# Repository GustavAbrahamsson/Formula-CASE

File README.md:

# Formula-CASE | Miniature Formula-style RC cars!

## ESP32-S3, FreeRTOS, 4WD

## F1-inspired custom steering wheel, with magnetic paddle shifters

## Remote control with "driver POV" video feed

## PCB

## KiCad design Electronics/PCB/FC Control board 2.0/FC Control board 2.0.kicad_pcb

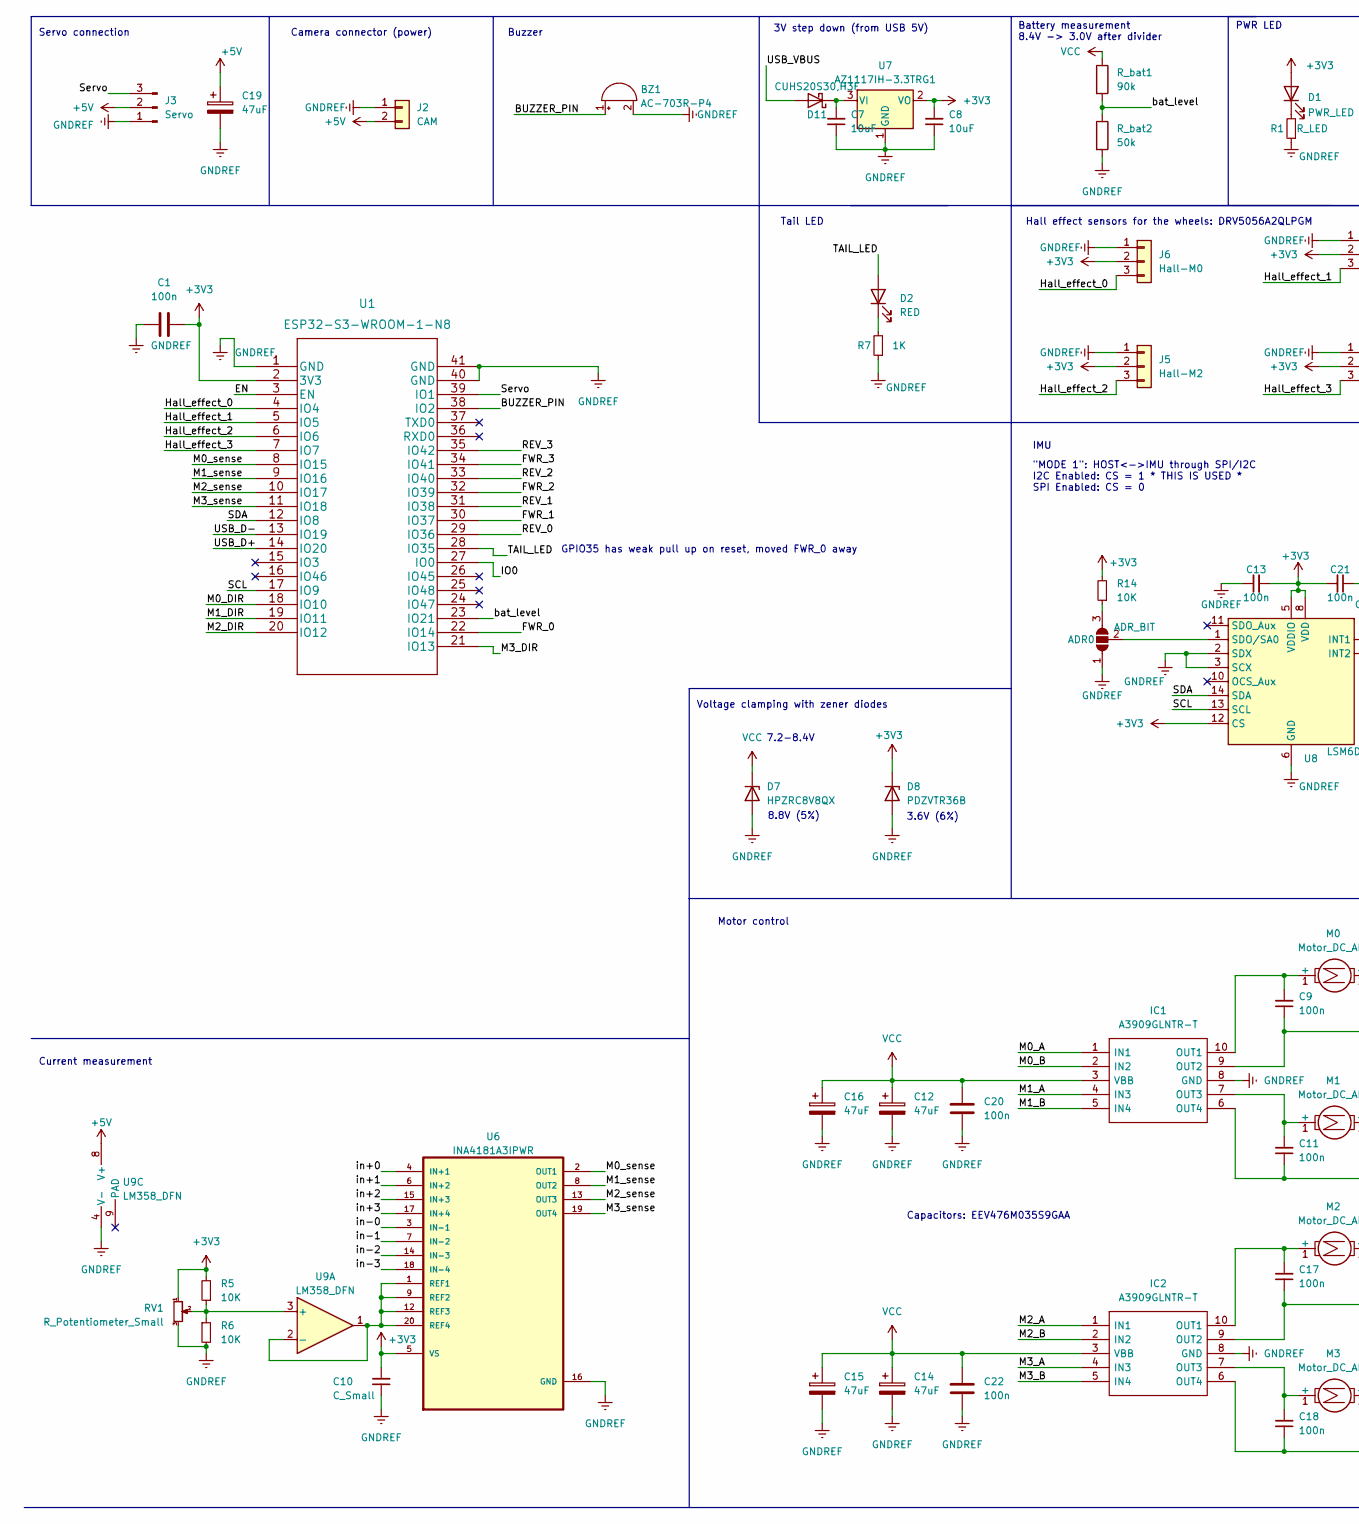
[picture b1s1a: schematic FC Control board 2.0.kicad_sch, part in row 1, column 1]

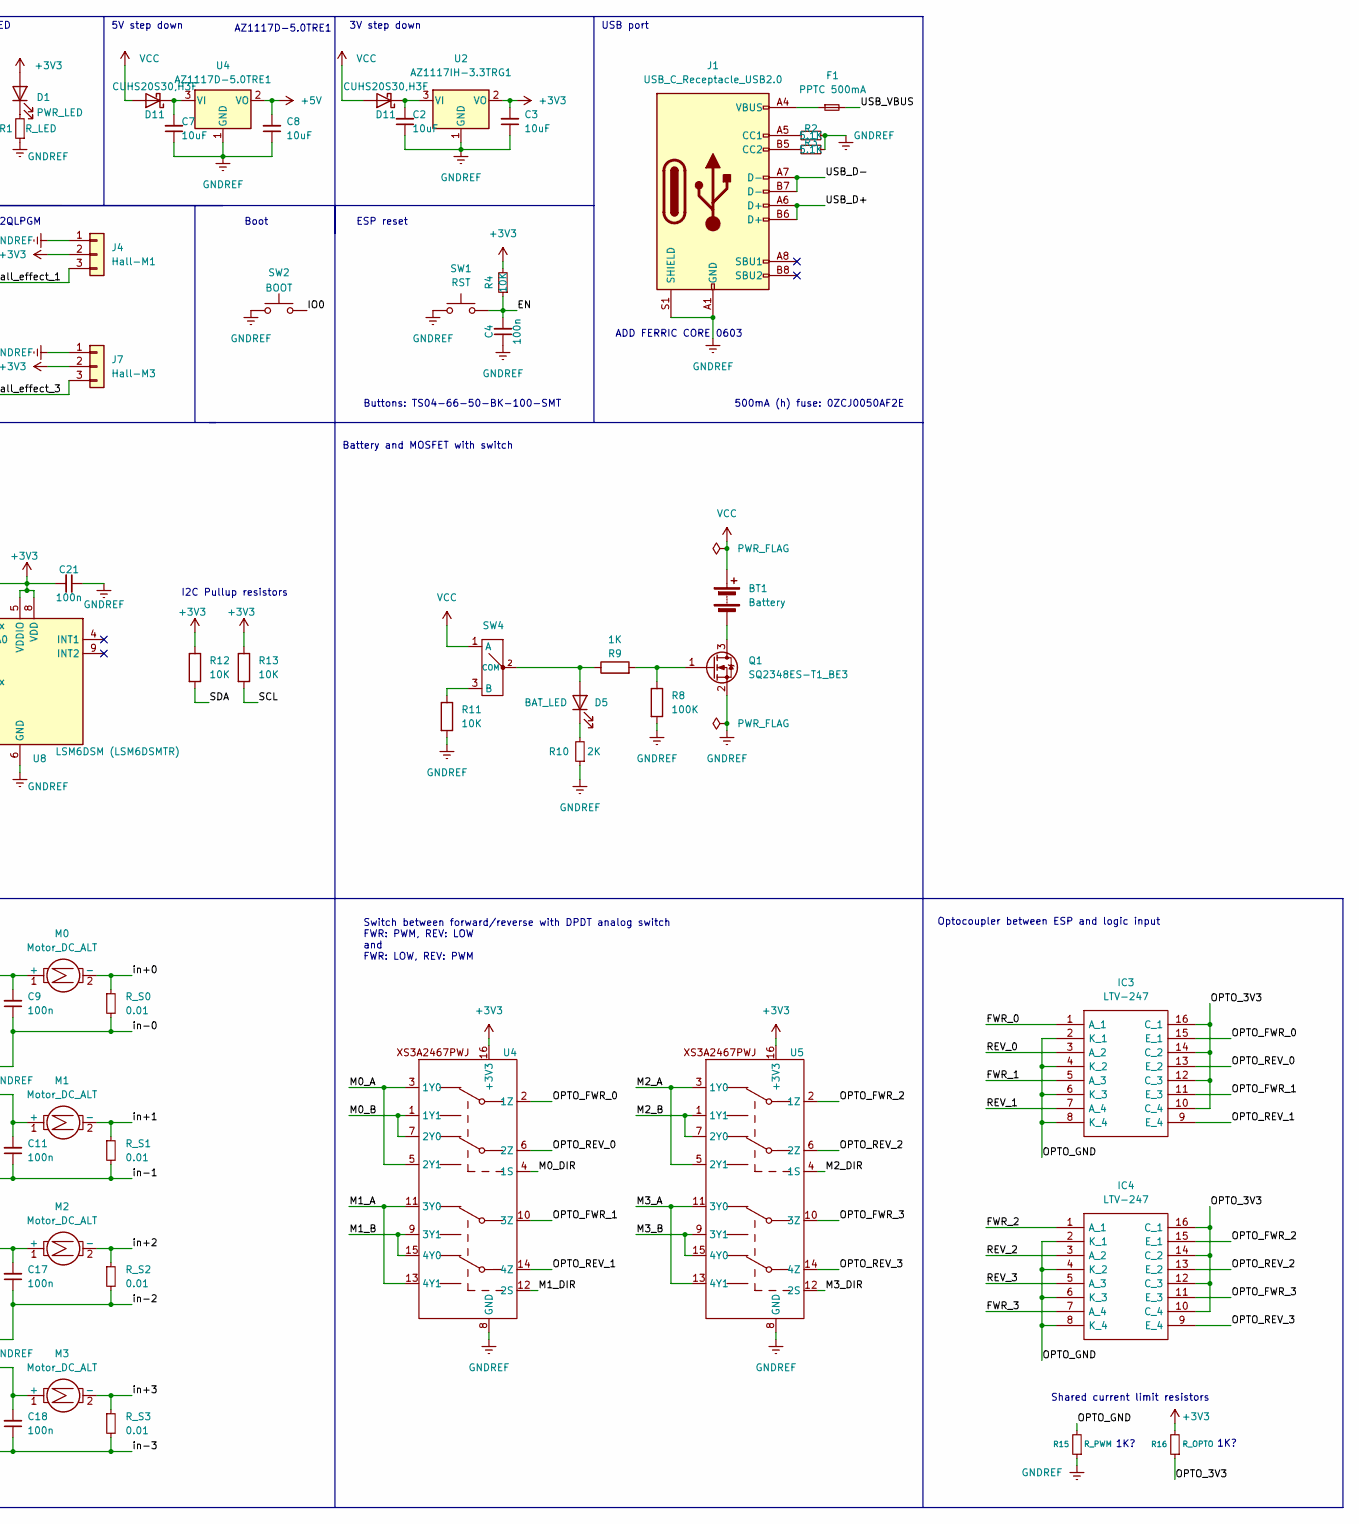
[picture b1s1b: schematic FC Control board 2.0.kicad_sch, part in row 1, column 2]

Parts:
ADR0: ADR_BIT; SolderJumper-3_P1.3mm_Open_RoundedPad1.0x1.5mm_NumberLabels
BT1: Battery; JST_EH_B2B-EH-A_1x02_P2.50mm_Vertical
BZ1: AC-703R-P4; MagneticBuzzer_Kobitone_254-EMB73-RO
C1, C9, C11, C17, C18, C20, C22: 100n; C_0603_1608Metric_Pad1.08x0.95mm_HandSolder
C2, C3, C7, C8: 10uF; C_1206_3216Metric
C4, C13, C21: 100n; C_0805_2012Metric_Pad1.18x1.45mm_HandSolder
C10: C_Small; C_0603_1608Metric
C12, C14, C15, C16, C19: 47uF; CP_Elec_6.3x5.4
D1: PWR_LED; LED_0805_2012Metric_Pad1.15x1.40mm_HandSolder
D2: RED; LED_D3.0mm
D5: BAT_LED; LED_0805_2012Metric_Pad1.15x1.40mm_HandSolder
D7: HPZRC8V8QX
D8: PDZVTR36B
D11: CUHS20S30,H3F
F1: PPTC 500mA; Fuse_1206_3216Metric
IC1, IC2: A3909GLNTR-T; SOP100P600X175-10N; Mouser Part Number 250-A3909GLNTR-T
IC3, IC4: LTV-247; LTV247; Mouser Part Number 859-LTV-247
J1: USB_C_Receptacle_USB2.0; USB_C_Receptacle_HRO_TYPE-C-31-M-12
J2: CAM; JST-ZH-2_PIN
J3: Servo; PinSocket_1x03_P2.54mm_Vertical
J4: Hall-M1; PinHeader_1x03_P1.27mm_Vertical
J5: Hall-M2; PinHeader_1x03_P1.27mm_Vertical
J6: Hall-M0; PinHeader_1x03_P1.27mm_Vertical
J7: Hall-M3; PinHeader_1x03_P1.27mm_Vertical
M0, M1, M2, M3: Motor_DC_ALT; JST_EH_B2B-EH-A_1x02_P2.50mm_Vertical
Q1: SQ2348ES-T1_BE3; SOT-23-3
R1: R_LED; R_0603_1608Metric_Pad0.98x0.95mm_HandSolder
R2, R3: 5.1K; R_0603_1608Metric_Pad0.98x0.95mm_HandSolder
R4, R5, R6, R11, R12, R13, R14: 10K; R_0603_1608Metric_Pad0.98x0.95mm_HandSolder
R7, R9: 1K; R_0603_1608Metric_Pad0.98x0.95mm_HandSolder
R8: 100K; R_0603_1608Metric_Pad0.98x0.95mm_HandSolder
R10: 2K; R_0603_1608Metric_Pad0.98x0.95mm_HandSolder
R15: R_PWM; R_0603_1608Metric_Pad0.98x0.95mm_HandSolder
R16: R_OPTO; R_0603_1608Metric_Pad0.98x0.95mm_HandSolder
RV1: R_Potentiometer_Small; PinHeader_1x03_P2.00mm_Vertical
R_S0, R_S1, R_S2, R_S3: 0.01; R_1206_3216Metric
R_bat1: 90k; R_0805_2012Metric_Pad1.20x1.40mm_HandSolder
R_bat2: 50k; R_0805_2012Metric_Pad1.20x1.40mm_HandSolder
SW1: RST; SW_Push_6x6mm_H9.5mm
SW2: BOOT; SW_Push_6x6mm_H9.5mm
SW4: LSS12-P-V-B
U1: ESP32-S3-WROOM-1-N8
U2, U7: AZ1117IH-3.3TRG1; SOT-223-3_TabPin2
U4, U5: XS3A2467PWJ _TSSOP-16_4.4x5mm_P0.65mm
U6: INA4181A3IPWR; SOP65P640X120-20N
U8: LSM6DSM (LSM6DSMTR); LSM6DSM
U9: LM358_DFN; SOIC-8-1EP_3.9x4.9mm_P1.27mm_EP2.514x3.2mm

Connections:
/BUZZER_PIN: BZ1.1 (-), U1.38 (IO2)
/EN: C4.2, R4.1, SW1.2, U1.3 (EN)
/FWR_0: IC3.1 (A_1), U1.22 (IO14)
/FWR_1: IC3.5 (A_3), U1.30 (IO37)
/FWR_2: IC4.1 (A_1), U1.32 (IO39)
/FWR_3: IC4.7 (A_4), U1.34 (IO41)
/Hall_effect_0: J6.3, U1.4 (IO4)
/Hall_effect_1: J4.3, U1.5 (IO5)
/Hall_effect_2: J5.3, U1.6 (IO6)
/Hall_effect_3: J7.3, U1.7 (IO7)
/IO0: SW2.2, U1.27 (IO0)
/M0_DIR: U1.18 (IO10), U4.4 (1S)
/M0_sense: U1.8 (IO15), U6.2 (OUT1)
/M1_A: IC1.4 (IN3), U4.11 (3Y0), U4.13 (4Y1)
/M1_B: IC1.5 (IN4), U4.9 (3Y1), U4.15 (4Y0)
/M1_DIR: U1.19 (IO11), U4.12 (2S)
/M1_sense: U1.9 (IO16), U6.8 (OUT2)
/M2_A: IC2.1 (IN1), U5.3 (1Y0), U5.5 (2Y1)
/M2_B: IC2.2 (IN2), U5.1 (1Y1), U5.7 (2Y0)
/M2_DIR: U1.20 (IO12), U5.4 (1S)
/M2_sense: U1.10 (IO17), U6.13 (OUT3)
/M3_A: IC2.4 (IN3), U5.11 (3Y0), U5.13 (4Y1)
/M3_B: IC2.5 (IN4), U5.9 (3Y1), U5.15 (4Y0)
/M3_DIR: U1.21 (IO13), U5.12 (2S)
/M3_sense: U1.11 (IO18), U6.19 (OUT4)
/OPTO_3V3: IC3.10 (C_4), IC3.12 (C_3), IC3.14 (C_2), IC3.16 (C_1), IC4.10 (C_4), IC4.12 (C_3), IC4.14 (C_2), IC4.16 (C_1), R16.1
/OPTO_FWR_1: IC3.11 (E_3), U4.10 (3Z)
/OPTO_FWR_2: IC4.15 (E_1), U5.2 (1Z)
/OPTO_FWR_3: IC4.11 (E_3), U5.10 (3Z)
/OPTO_GND: IC3.2 (K_1), IC3.4 (K_2), IC3.6 (K_3), IC3.8 (K_4), IC4.2 (K_1), IC4.4 (K_2), IC4.6 (K_3), IC4.8 (K_4), R15.2
/OPTO_REV_0: IC3.13 (E_2), U4.6 (2Z)
/OPTO_REV_1: IC3.9 (E_4), U4.14 (4Z)
/OPTO_REV_2: IC4.13 (E_2), U5.6 (2Z)
/OPTO_REV_3: IC4.9 (E_4), U5.14 (4Z)
/REV_0: IC3.3 (A_2), U1.29 (IO36)
/REV_1: IC3.7 (A_4), U1.31 (IO38)
/REV_2: IC4.3 (A_2), U1.33 (IO40)
/REV_3: IC4.5 (A_3), U1.35 (IO42)
/SCL: R13.2, U1.17 (IO9), U8.13 (SCL)
/SDA: R12.2, U1.12 (IO8), U8.14 (SDA)
/Servo: J3.3, U1.39 (IO1)
/TAIL_LED: D2.2 (A), U1.28 (IO35)
/USB_D+: J1.A6 (D+), J1.B6 (D+), U1.14 (IO20)
/USB_D-: J1.A7 (D-), J1.B7 (D-), U1.13 (IO19)
/bat_level: R_bat1.2, R_bat2.1, U1.23 (IO21)
/in+0: M0.2 (-), R_S0.1, U6.4 (IN+1)
/in+1: M1.2 (-), R_S1.1, U6.6 (IN+2)
/in+2: M2.2 (-), R_S2.1, U6.15 (IN+3)
/in+3: M3.2 (-), R_S3.1, U6.17 (IN+4)
/in-0: C9.1, IC1.9 (OUT2), R_S0.2, U6.3 (IN-1)
/in-1: C11.1, IC1.6 (OUT4), R_S1.2, U6.7 (IN-2)
/in-2: C17.1, IC2.9 (OUT2), R_S2.2, U6.14 (IN-3)
/in-3: C18.1, IC2.6 (OUT4), R_S3.2, U6.18 (IN-4)
unnamed: ADR0.3 (B), R14.1
unnamed: ADR0.2 (C), U8.1 (SDO/SA0)
unnamed: BT1.2 (-), Q1.3 (D)
unnamed: D1.1 (K), R1.2
unnamed: D2.1 (K), R7.2
unnamed 59: C2.2, U2.3 (VI); also elsewhere on the board
unnamed: D5.2 (A), R9.1, SW4.2 (COM)
unnamed: D5.1 (K), R10.2
unnamed 62: J1.A4 (VBUS), J1.A9 (VBUS), J1.B4 (VBUS), J1.B9 (VBUS); also elsewhere on the board
unnamed: C9.2, IC1.10 (OUT1), M0.1 (+)
unnamed: C11.2, IC1.7 (OUT3), M1.1 (+)
unnamed: C17.2, IC2.10 (OUT1), M2.1 (+)
unnamed: C18.2, IC2.7 (OUT3), M3.1 (+)
unnamed: J1.A5 (CC1), R2.1
unnamed: J1.B5 (CC2), R3.1
unnamed: Q1.1 (G), R8.1, R9.2
unnamed: R11.1, SW4.3 (B)
unnamed: U6.1 (REF1), U6.9 (REF2), U6.12 (REF3), U6.20 (REF4), U9.1, U9.2 (-)
unnamed: R5.1, R6.1, RV1.2, U9.3 (+)
VCC: BT1.1 (+), C12.1, C14.1, C15.1, C16.1, C20.2, C22.2, D7.1 (K), IC1.3 (VBB), IC2.3 (VBB), R_bat1.1, SW4.1 (A); also elsewhere on the board

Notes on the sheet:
Boot
1K?
I2C Pullup resistors
Buzzer
Switch between forward/reverse with DPDT analog switch FWR: PWM, REV: LOW and FWR: LOW, REV: PWM
Tail LED
3V step down (from USB 5V)
500mA (h) fuse: 0ZCJ0050AF2E
Shared current limit resistors
"MODE 1": HOST<->IMU through SPI/I2C I2C Enabled: CS = 1 * THIS IS USED * SPI Enabled: CS = 0
AZ1117D-5.0TRE1
Buttons: TS04-66-50-BK-100-SMT
USB port
IMU
7.2-8.4V
Capacitors: EEV476M035S9GAA
Motor control
Servo connection
Battery measurement 8.4V -> 3.0V after divider
ESP reset
Current measurement
8.8V (5%)
ADD FERRIC CORE 0603
Camera connector (power)
PWR LED
3.6V (6%)
Battery and MOSFET with switch
3V step down
Optocoupler between ESP and logic input
5V step down
Voltage clamping with zener diodes
Hall effect sensors for the wheels: DRV5056A2QLPGM
GPIO35 has weak pull up on reset, moved FWR_0 away

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
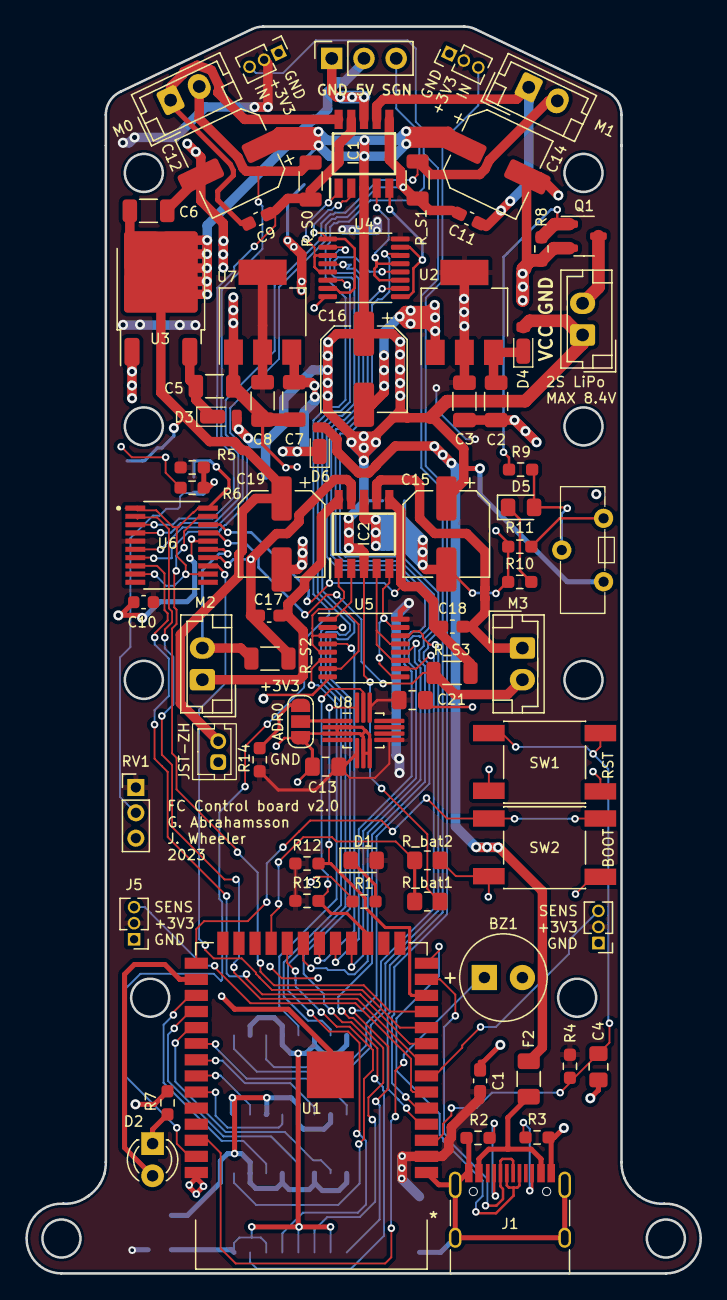
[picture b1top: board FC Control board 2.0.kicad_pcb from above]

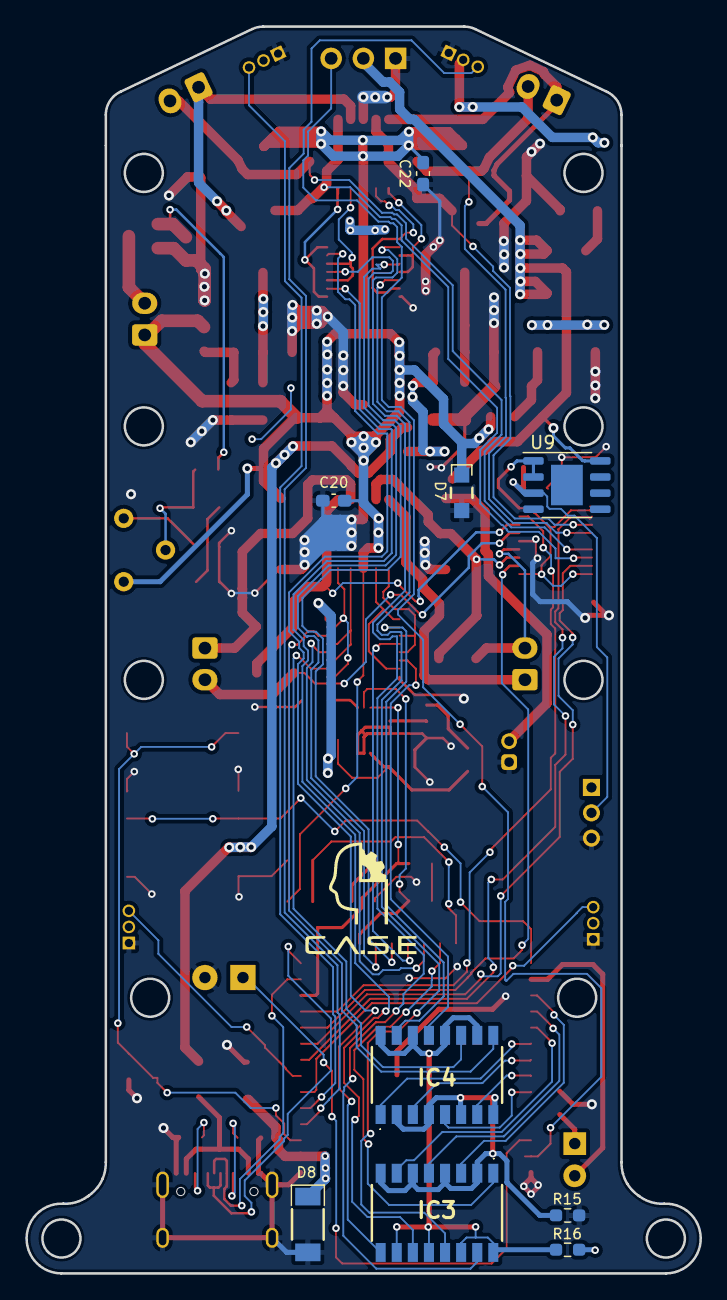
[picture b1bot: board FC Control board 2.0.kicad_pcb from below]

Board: 2 copper layers, 53.2 x 98.4 mm, 85 parts (9 on the bottom side), 82 nets.

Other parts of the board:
C5, C6: 10uF; C_1206_3216Metric
D3, D4, D6: CUHS20S30,H3F
F2: PPTC 500mA; Fuse_1206_3216Metric
U3: AZ1117D-5.0TRE1; TO-252-2

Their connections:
/USB_VBUS: D6.2 (A), F2.2
unnamed 59: D4.1 (K); also elsewhere on the board
unnamed 62: F2.1; also elsewhere on the board
VCC: D3.2 (A), D4.2 (A); also elsewhere on the board

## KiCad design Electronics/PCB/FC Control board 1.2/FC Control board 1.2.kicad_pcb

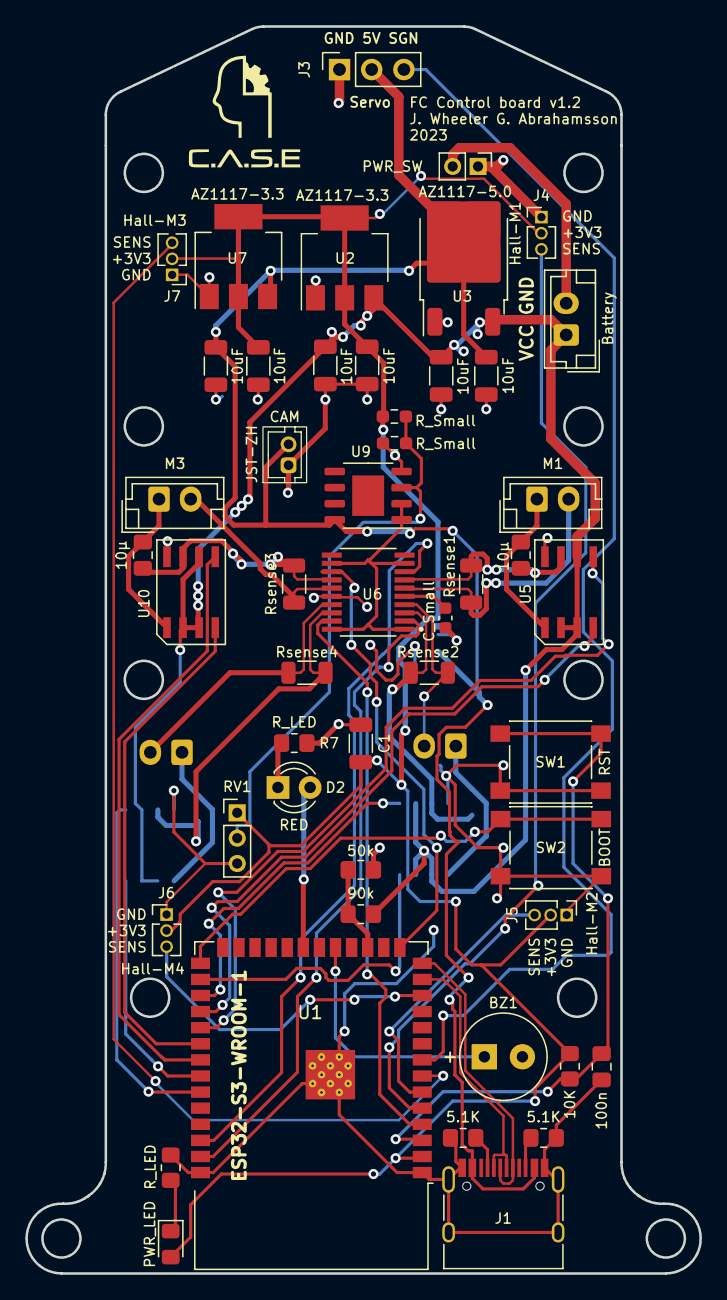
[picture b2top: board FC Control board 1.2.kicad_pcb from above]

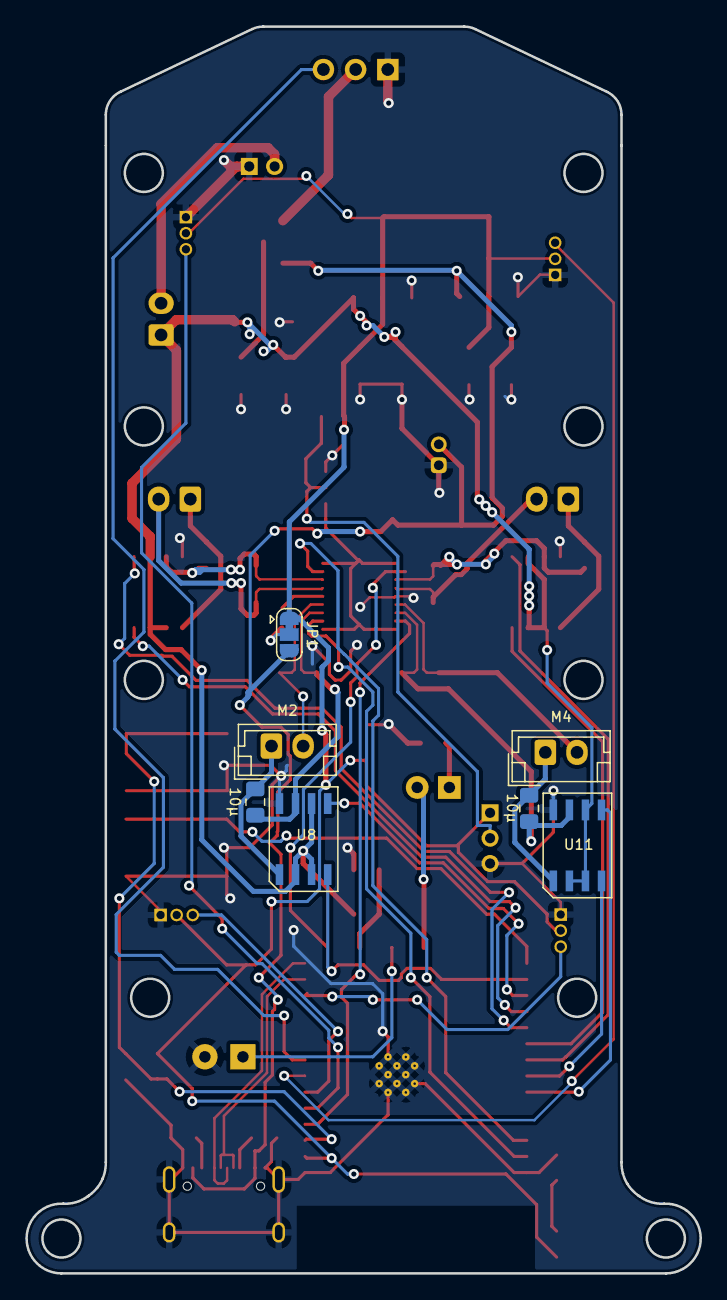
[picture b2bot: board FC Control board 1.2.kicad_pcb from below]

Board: 2 copper layers, 53.2 x 98.4 mm, 56 parts (7 on the bottom side), 49 nets.

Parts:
BT1: Battery; JST_EH_B2B-EH-A_1x02_P2.50mm_Vertical
BZ1: AC-703R-P4; MagneticBuzzer_Kobitone_254-EMB73-RO
C1: C; C_1206_3216Metric
C2, C3, C5, C6, C7, C8: 10uF; C_1206_3216Metric
C4: 100n; C_0805_2012Metric_Pad1.18x1.45mm_HandSolder
C10: C_Small; C_0603_1608Metric
C11, C12, C13, C14: 10µ; C_0805_2012Metric_Pad1.18x1.45mm_HandSolder
D1: PWR_LED; LED_0805_2012Metric_Pad1.15x1.40mm_HandSolder
D2: RED; LED_D3.0mm
J1: USB_C_Receptacle_USB2.0; USB_C_Receptacle_HRO_TYPE-C-31-M-12
J2: CAM; JST-ZH-2_PIN
J3: Servo; PinSocket_1x03_P2.54mm_Vertical
J4: Hall-M1; PinHeader_1x03_P1.27mm_Vertical
J5: Hall-M2; PinHeader_1x03_P1.27mm_Vertical
J6: Hall-M4; PinHeader_1x03_P1.27mm_Vertical
J7: Hall-M3; PinHeader_1x03_P1.27mm_Vertical
JP1: SolderJumper_3_Bridged12; SolderJumper-3_P1.3mm_Bridged12_RoundedPad1.0x1.5mm
M1, M2, M3, M4: Motor_DC_ALT; JST_EH_B2B-EH-A_1x02_P2.50mm_Vertical
R1, R7: R_LED; R_0805_2012Metric_Pad1.20x1.40mm_HandSolder
R2, R3: 5.1K; R_0805_2012Metric_Pad1.20x1.40mm_HandSolder
R4: 10K; R_0805_2012Metric_Pad1.20x1.40mm_HandSolder
R5, R6: R_Small; R_0603_1608Metric_Pad0.98x0.95mm_HandSolder
RV1: R_Potentiometer_Small; PinHeader_1x03_P2.00mm_Vertical
R_bat1: 90k; R_0805_2012Metric_Pad1.20x1.40mm_HandSolder
R_bat2: 50k; R_0805_2012Metric_Pad1.20x1.40mm_HandSolder
Rsense1, Rsense2, Rsense3, Rsense4: R_Small; R_1206_3216Metric
SW1: RST; SW_Push_1P1T_NO_6x6mm_H9.5mm
SW2: BOOT; SW_Push_1P1T_NO_6x6mm_H9.5mm
SW3: PWR_SW; PinHeader_1x02_P2.00mm_Vertical
U1: ESP32-S3-WROOM-1-N8; ESP32-S3-WROOM-1
U2, U7: AZ1117-3.3; SOT-223-3_TabPin2
U3: AZ1117-5.0; TO-252-2
U5, U8, U10, U11: ZXBM5210
U6: INA4181A3IPWR; SOP65P640X120-20N
U9: LM358_DFN; SOIC-8-1EP_3.9x4.9mm_P1.27mm_EP2.514x3.2mm

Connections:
+3V3: C1.2, C3.2, C8.2, D1.2 (A), J4.2, J5.2, J6.2, J7.2, JP1.1 (A), R4.2, R5.2, RV1.1, U1.2 (3V3), U2.2 (VO), U7.2 (VO)
+5V: C6.2, C7.2, J1.A4 (VBUS), J1.A9 (VBUS), J1.B4 (VBUS), J1.B9 (VBUS), J2.2, J3.2, JP1.3 (B), U3.2 (VO), U7.3 (VI), U9.8 (V+)
/ADC1_8: R_bat1.2, R_bat2.1, U1.17 (IO9)
/BUZZER_PIN: BZ1.1 (-), U1.19 (IO11)
/EN: C4.2, R4.1, SW1.2, U1.3 (EN)
/FWR_1: U1.28 (IO35), U8.4 (FWD)
/FWR_2: U1.30 (IO37), U5.4 (FWD)
/FWR_3: U1.32 (IO39), U10.4 (FWD)
/FWR_4: U1.34 (IO41), U11.4 (FWD)
/Hall_effect_1: J4.3, U1.5 (IO5)
/Hall_effect_2: J5.3, U1.6 (IO6)
/Hall_effect_3: J7.3, U1.7 (IO7)
/Hall_effect_4: J6.3, U1.12 (IO8)
/IO0: SW2.2, U1.27 (IO0)
/M1_sense: U1.39 (IO1), U6.2 (OUT1)
/M2_sense: U1.38 (IO2), U6.8 (OUT2)
/M3_sense: U1.15 (IO3), U6.13 (OUT3)
/M4_sense: U1.4 (IO4), U6.19 (OUT4)
/REV_1: U1.29 (IO36), U8.5 (REV)
/REV_2: U1.31 (IO38), U5.5 (REV)
/REV_3: U1.33 (IO40), U10.5 (REV)
/REV_4: U1.35 (IO42), U11.5 (REV)
/Servo: J3.3, U1.8 (IO15)
/TAIL_LED: D2.2 (A), U1.21 (IO13)
/USB_D+: J1.A6 (D+), J1.B6 (D+), U1.14 (IO20)
/USB_D-: J1.A7 (D-), J1.B7 (D-), U1.13 (IO19)
/in+1: M2.2 (-), Rsense2.1, U6.4 (IN+1)
/in+2: M1.2 (-), Rsense1.1, U6.6 (IN+2)
/in+3: M3.2 (-), Rsense3.1, U6.15 (IN+3)
/in+4: M4.2 (-), Rsense4.1, U6.17 (IN+4)
/in-1: C11.2, Rsense2.2, U6.3 (IN-1), U8.7 (OUT2)
/in-2: C12.2, Rsense1.2, U5.7 (OUT2), U6.7 (IN-2)
/in-3: C13.2, Rsense3.2, U6.14 (IN-3), U10.7 (OUT2)
/in-4: C14.2, Rsense4.2, U6.18 (IN-4), U11.7 (OUT2)
GNDREF: BZ1.2 (+), C1.1, C2.1, C3.1, C4.1, C5.1, C6.1, C7.1, C8.1, J1.A1 (GND), J1.A12 (GND), J1.B1 (GND), J1.B12 (GND), J1.S1 (SHIELD), J2.1, J3.1, J4.1, J5.1, J6.1, J7.1, R1.1, R2.2, R3.2, R6.2, R7.1, RV1.3, R_bat2.2, SW1.1, SW2.1, SW3.1 (A), U1.1 (GND), U1.40 (GND), U1.41 (GND), U2.1 (GND), U3.1 (GND), U5.8 (GND), U6.16 (GND), U7.1 (GND), U8.8 (GND), U9.4 (V-), U10.8 (GND), U11.8 (GND)
unnamed: BT1.2 (-), SW3.2 (B)
unnamed: D1.1 (K), R1.2
unnamed: D2.1 (K), R7.2
unnamed: J1.A5 (CC1), R2.1
unnamed: J1.B5 (CC2), R3.1
unnamed: C10.1, JP1.2 (C)
unnamed: C12.1, M1.1 (+), U5.1 (Out1)
unnamed: C11.1, M2.1 (+), U8.1 (Out1)
unnamed: C13.1, M3.1 (+), U10.1 (Out1)
unnamed: C14.1, M4.1 (+), U11.1 (Out1)
unnamed: U6.1 (REF1), U6.9 (REF2), U6.12 (REF3), U6.20 (REF4), U9.1, U9.2 (-)
unnamed: C10.2, U6.5 (VS)
unnamed: R5.1, R6.1, RV1.2, U9.3 (+)
VCC: BT1.1 (+), C2.2, C5.2, R_bat1.1, U2.3 (VI), U3.3 (VI), U5.2 (Vm), U5.3 (Vdd), U5.6 (Vref), U8.2 (Vm), U8.3 (Vdd), U8.6 (Vref), U10.2 (Vm), U10.3 (Vdd), U10.6 (Vref), U11.2 (Vm), U11.3 (Vdd), U11.6 (Vref)

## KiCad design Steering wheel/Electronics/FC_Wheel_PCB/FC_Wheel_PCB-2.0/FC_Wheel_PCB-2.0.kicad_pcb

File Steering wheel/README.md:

# FC_Wheel PCB
## v1.0
### Issues:
- The pads for the ESP32-S3 footprint are too small 
- The ESP receives 2.4V even though the LDO outputs 3.3V
  - Use larger vias
- The BOOT and RESET push-buttons need to be more accessable and easier to press
  - Use 'longer' push-buttons with the same footprint
- The battery pins need labels
- The holes are not aligned for the MPU6050 footprint
- Cables
  - Move to a single PCB with no cables

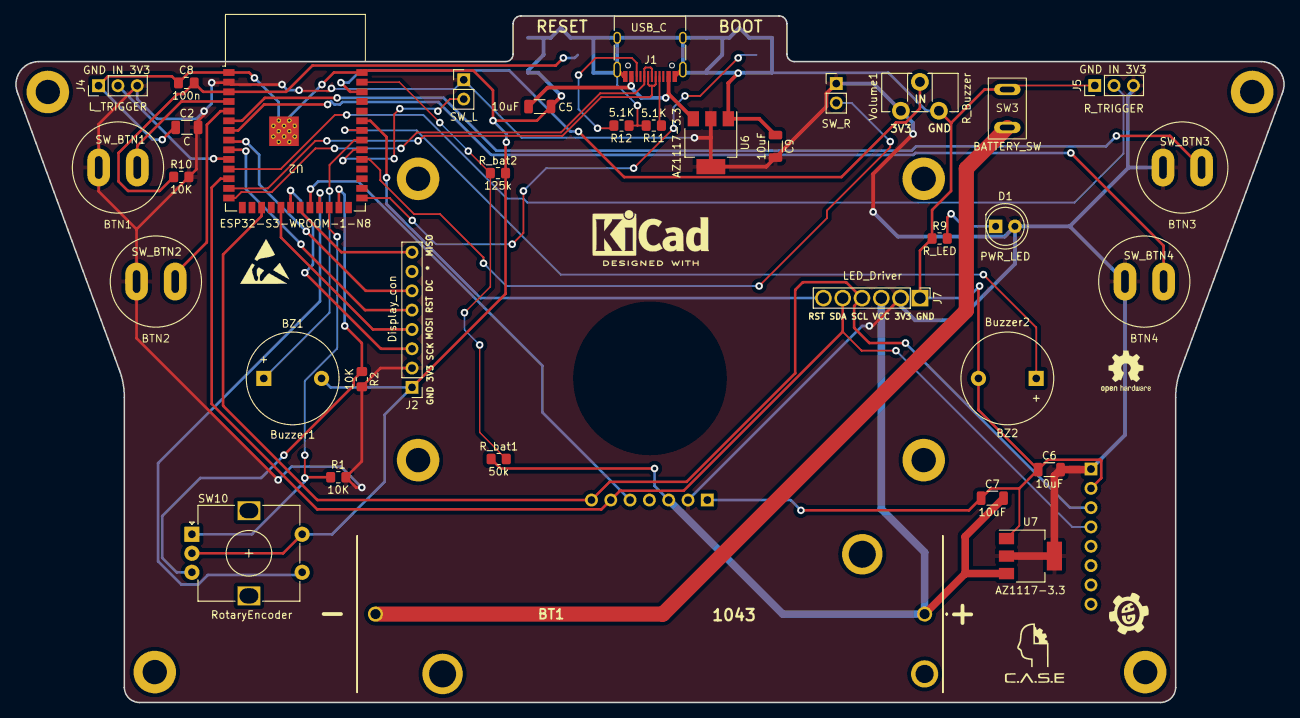
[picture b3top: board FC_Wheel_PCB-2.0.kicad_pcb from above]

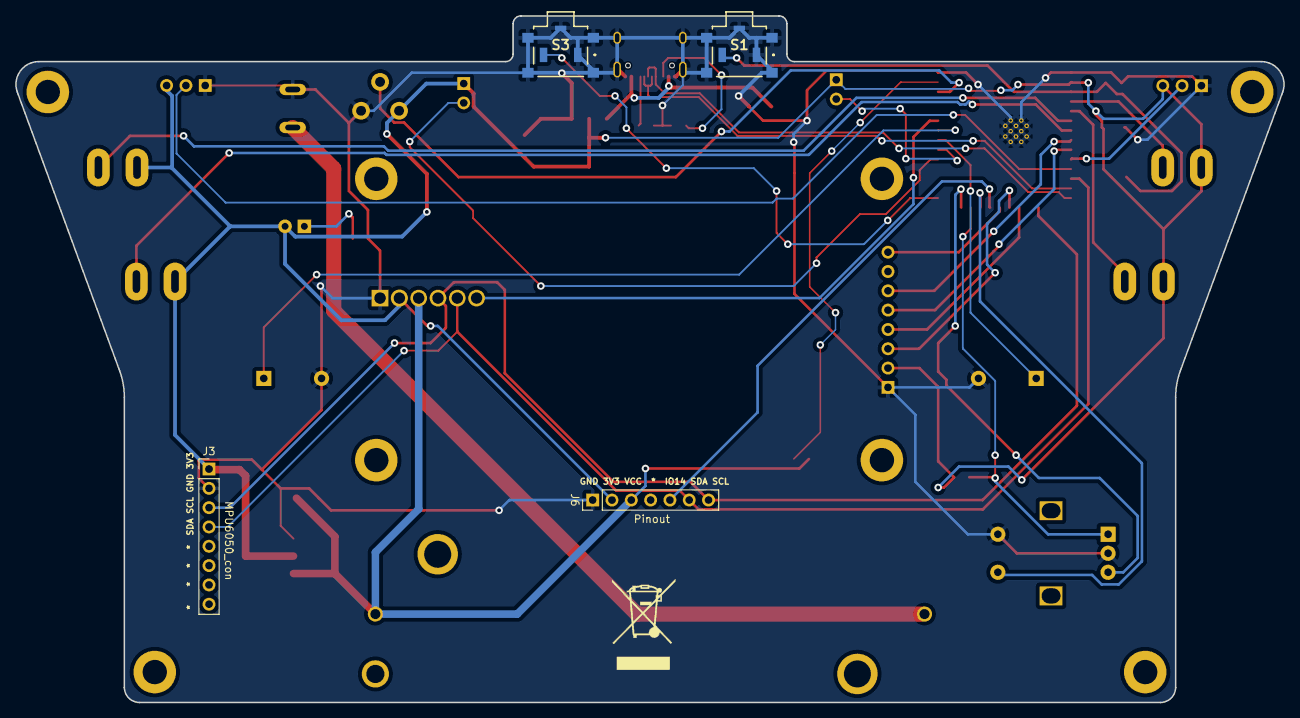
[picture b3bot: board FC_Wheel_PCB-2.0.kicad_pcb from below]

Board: 2 copper layers, 166.8 x 90.3 mm, 39 parts (4 on the bottom side), 36 nets.

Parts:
BT1: Battery; 1043_fromMouser
BTN1: SW_BTN1; SPST_PushButton_Cyl
BTN2: SW_BTN2; SPST_PushButton_Cyl
BTN3: SW_BTN3; SPST_PushButton_Cyl
BTN4: SW_BTN4; SPST_PushButton_Cyl
BZ1: Buzzer1; Buzzer_12x9.5RM7.6
BZ2: Buzzer2; Buzzer_12x9.5RM7.6
C2: C; C_1206_3216Metric
C5, C6, C7, C9: 10uF; C_1206_3216Metric
C8: 100n; C_0805_2012Metric_Pad1.18x1.45mm_HandSolder
D1: PWR_LED; LED_D5.0mm
J1: USB_C; USB_C_Receptacle_HRO_TYPE-C-31-M-12
J2: Display_con; PinHeader_1x08_P2.54mm_Vertical
J3: MPU6050_con; PinHeader_1x08_P2.54mm_Vertical
J4: L_TRIGGER; PinHeader_1x03_P2.54mm_Vertical
J5: R_TRIGGER; PinHeader_1x03_P2.54mm_Vertical
J6: Pinout; PinHeader_1x07_P2.54mm_Vertical
J7: LED_Driver; PinHeader_1x06_P2.54mm_Vertical
PADDLE1: SW_R; PinHeader_1x02_P2.54mm_Vertical
PADDLE2: SW_L; PinHeader_1x02_P2.54mm_Vertical
R1, R2, R10: 10K; R_0805_2012Metric_Pad1.20x1.40mm_HandSolder
R9: R_LED; R_0805_2012Metric_Pad1.20x1.40mm_HandSolder
R11, R12: 5.1K; R_0805_2012Metric_Pad1.20x1.40mm_HandSolder
R_bat1: 50k; R_0805_2012Metric_Pad1.20x1.40mm_HandSolder
R_bat2: 125k; R_0805_2012Metric_Pad1.20x1.40mm_HandSolder
S1, S3: TL3336AF160Q
SW3: BATTERY_SW; STST Switch 2MS6T1B3M2QES
SW10: RotaryEncoder; RotaryEncoder_Alps_EC12E-Switch_Vertical_H20mm
U2: ESP32-S3-WROOM-1-N8; ESP32-S3-WROOM-1_handsolder
U6, U7: AZ1117-3.3; SOT-223-3_TabPin2
Volume1: R_Buzzer; Potentiometer_ACP_CA9-H3,8_Horizontal

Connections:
+3V3: BTN1.1 (A), BTN2.1 (A), BTN3.1 (A), BTN4.1 (A), C2.2, C6.2, C9.2, D1.2 (A), J2.2, J3.1, J4.3, J5.3, J6.2, J7.2, PADDLE1.1 (A), PADDLE2.1 (A), R1.2, R2.2, R10.2, U2.2 (3V3), U6.2 (VO), U7.2 (VO), Volume1.1
+5V: C5.2, J1.A4 (VBUS), J1.A9 (VBUS), J1.B4 (VBUS), J1.B9 (VBUS), U6.3 (VI)
/BTN1: BTN1.2 (B), U2.4 (IO4)
/BTN2: BTN2.2 (B), U2.5 (IO5)
/BTN3: BTN3.2 (B), U2.6 (IO6)
/BTN4: BTN4.2 (B), U2.7 (IO7)
/BUZZER_PIN1: BZ1.1 (-), U2.33 (IO40)
/BUZZER_PIN2: BZ2.1 (-), U2.34 (IO41)
/DC: J2.6, U2.8 (IO15)
/EN: C8.2, R10.1, S1.2 (NO), U2.3 (EN)
/ENC_A: R1.1, SW10.A, U2.24 (IO47)
/ENC_B: R2.1, SW10.B, U2.25 (IO48)
/ENC_SW: SW10.S2, U2.23 (IO21)
/IO0: S3.2 (NO), U2.27 (IO0)
/IO14: J6.5, U2.22 (IO14)
/LED_RESET: J7.6, U2.35 (IO42)
/L_PADDLE: PADDLE2.2 (B), U2.32 (IO39)
/L_TRIGGER: J4.2, U2.10 (IO17)
/MISO: J2.8, U2.21 (IO13)
/MOSI: J2.4, U2.19 (IO11)
/RST: J2.5, U2.9 (IO16)
/R_PADDLE: PADDLE1.2 (B), U2.31 (IO38)
/R_TRIGGER: J5.2, U2.11 (IO18)
/SCK: J2.3, U2.20 (IO12)
/SCL: J3.3, J6.7, J7.4, U2.17 (IO9)
/SDA: J3.4, J6.6, J7.5, U2.12 (IO8)
/USB_D+: J1.A6 (D+), J1.B6 (D+), U2.14 (IO20)
/USB_D-: J1.A7 (D-), J1.B7 (D-), U2.13 (IO19)
/Volume_pot: U2.38 (IO2), Volume1.2
/bat_level: R_bat1.2, R_bat2.1, U2.39 (IO1)
Earth: BZ1.2 (+), BZ2.2 (+), C2.1, C5.1, C6.1, C7.1, C8.1, C9.1, J1.A1 (GND), J1.A12 (GND), J1.B1 (GND), J1.B12 (GND), J1.S1 (SHIELD), J2.1, J3.2, J4.1, J5.1, J6.1, J7.1, R9.1, R11.2, R12.2, R_bat2.2, S1.1 (COM), S1.MP1, S1.MP2, S1.MP3, S1.MP4, S1.MP5, S3.1 (COM), S3.MP1, S3.MP2, S3.MP3, S3.MP4, S3.MP5, SW3.1 (A), SW10.C, SW10.S1, U2.1 (GND), U2.40 (GND), U2.41 (GND), U6.1 (GND), U7.1 (GND), Volume1.3
unnamed: BT1.2 (-), SW3.2 (B)
unnamed: D1.1 (K), R9.2
unnamed: J1.A5 (CC1), R11.1
unnamed: J1.B5 (CC2), R12.1
VCC: BT1.1 (+), C7.2, J6.3, J7.3, R_bat1.1, U7.3 (VI)

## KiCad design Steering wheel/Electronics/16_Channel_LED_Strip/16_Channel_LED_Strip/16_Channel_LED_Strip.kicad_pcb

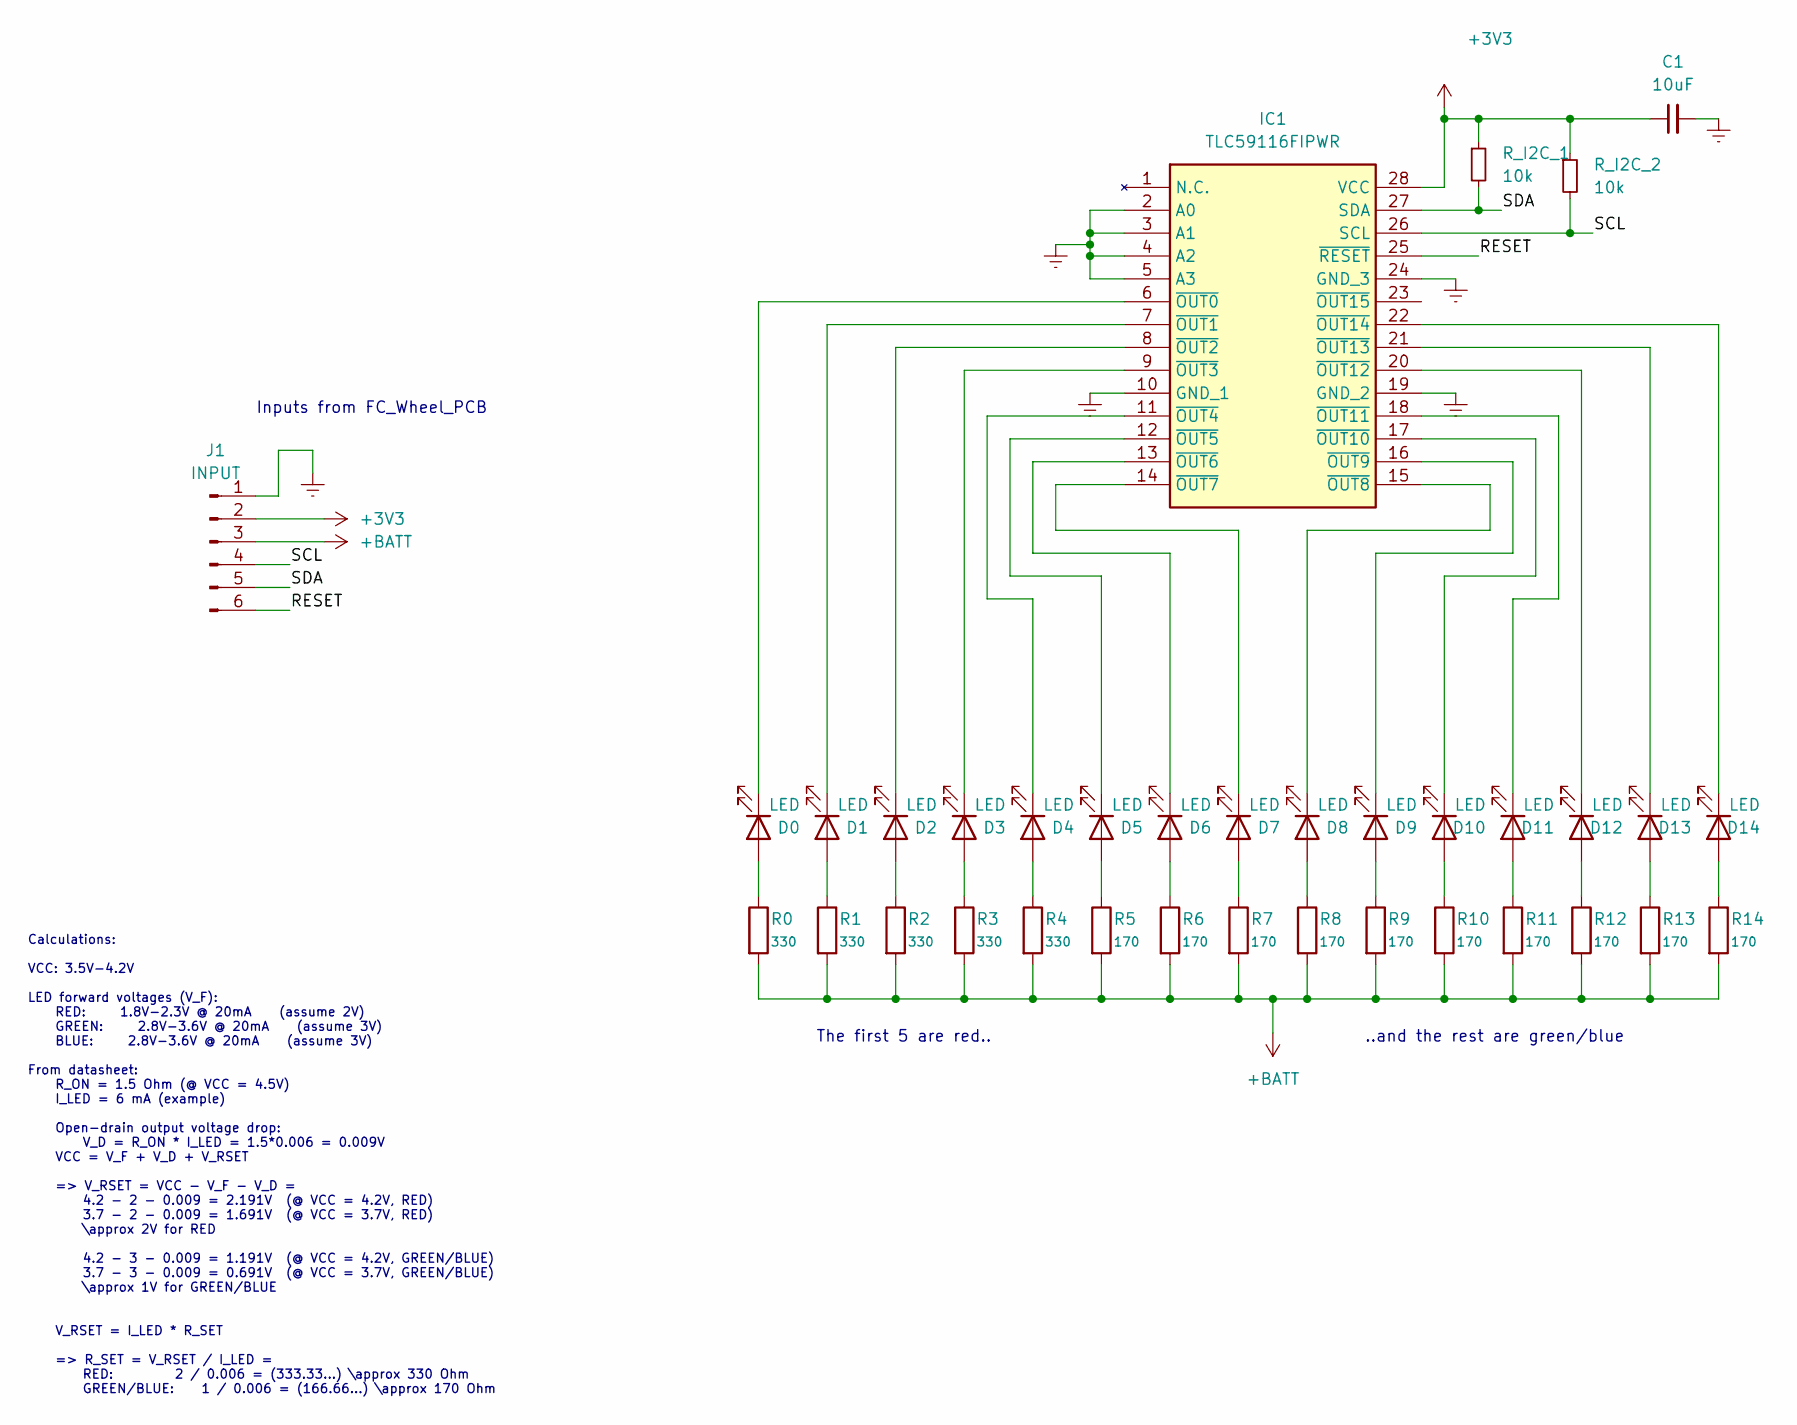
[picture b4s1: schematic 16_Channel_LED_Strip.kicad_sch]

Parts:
C1: 10uF; C_0805_2012Metric_Pad1.18x1.45mm_HandSolder
D0, D1, D2, D3, D4, D5, D6, D7, D8, D9, D10, D11, D12, D13, D14: LED; LED_D5.0mm
IC1: TLC59116FIPWR; SOP65P640X120-28N; Mouser Part Number 595-TLC59116FIPWR
J1: INPUT; PinHeader_1x06_P2.54mm_Vertical
R0, R1, R2, R3, R4: 330; R_0805_2012Metric_Pad1.20x1.40mm_HandSolder
R5, R6, R7, R8, R9, R10, R11, R12, R13, R14: 170; R_0805_2012Metric_Pad1.20x1.40mm_HandSolder
R_I2C_1, R_I2C_2: 10k; R_0805_2012Metric_Pad1.20x1.40mm_HandSolder

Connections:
+3V3: C1.1, IC1.28 (VCC), J1.2, R_I2C_1.1, R_I2C_2.1
+BATT: J1.3, R0.2, R1.2, R2.2, R3.2, R4.2, R5.2, R6.2, R7.2, R8.2, R9.2, R10.2, R11.2, R12.2, R13.2, R14.2
/RESET: IC1.25 (~RESET), J1.6
/SCL: IC1.26 (SCL), J1.4, R_I2C_2.2
/SDA: IC1.27 (SDA), J1.5, R_I2C_1.2
Earth: C1.2, IC1.2 (A0), IC1.3 (A1), IC1.4 (A2), IC1.5 (A3), IC1.10 (GND_1), IC1.19 (GND_2), IC1.24 (GND_3), J1.1
unnamed: D0.2 (A), R0.1
unnamed: D0.1 (K), IC1.6 (~OUT0)
unnamed: D1.2 (A), R1.1
unnamed: D1.1 (K), IC1.7 (~OUT1)
unnamed: D2.2 (A), R2.1
unnamed: D2.1 (K), IC1.8 (~OUT2)
unnamed: D3.2 (A), R3.1
unnamed: D3.1 (K), IC1.9 (~OUT3)
unnamed: D4.2 (A), R4.1
unnamed: D4.1 (K), IC1.11 (~OUT4)
unnamed: D5.2 (A), R5.1
unnamed: D5.1 (K), IC1.12 (~OUT5)
unnamed: D6.2 (A), R6.1
unnamed: D6.1 (K), IC1.13 (~OUT6)
unnamed: D7.2 (A), R7.1
unnamed: D7.1 (K), IC1.14 (~OUT7)
unnamed: D8.2 (A), R8.1
unnamed: D8.1 (K), IC1.15 (~OUT8)
unnamed: D9.2 (A), R9.1
unnamed: D9.1 (K), IC1.16 (~OUT9)
unnamed: D10.2 (A), R10.1
unnamed: D10.1 (K), IC1.17 (~OUT10)
unnamed: D11.2 (A), R11.1
unnamed: D11.1 (K), IC1.18 (~OUT11)
unnamed: D12.2 (A), R12.1
unnamed: D12.1 (K), IC1.20 (~OUT12)
unnamed: D13.2 (A), R13.1
unnamed: D13.1 (K), IC1.21 (~OUT13)
unnamed: D14.2 (A), R14.1
unnamed: D14.1 (K), IC1.22 (~OUT14)

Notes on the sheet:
The first 5 are red..
Inputs from FC_Wheel_PCB
..and the rest are green/blue
Calculations: VCC: 3.5V-4.2V LED forward voltages (V_F): RED: 1.8V-2.3V @ 20mA (assume 2V) GREEN: 2.8V-3.6V @ 20mA (assume 3V) BLUE: 2.8V-3.6V @ 20mA (assume 3V) From datasheet: R_ON = 1.5 Ohm (@ VCC = 4.5V) I_LED = 6 mA (example) Open-drain output voltage drop: V_D = R_ON * I_LED = 1.5*0.006 = 0.0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
